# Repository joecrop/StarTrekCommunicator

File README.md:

# StarTrekCommunicator
In the true spirit of Star Trek, this communicator badge is completely autonomous, while fitting in the form factor of an original badge

<a href="https://hackaday.io/project/19700-star-trek-communicator-badge">Hackaday Project</a>

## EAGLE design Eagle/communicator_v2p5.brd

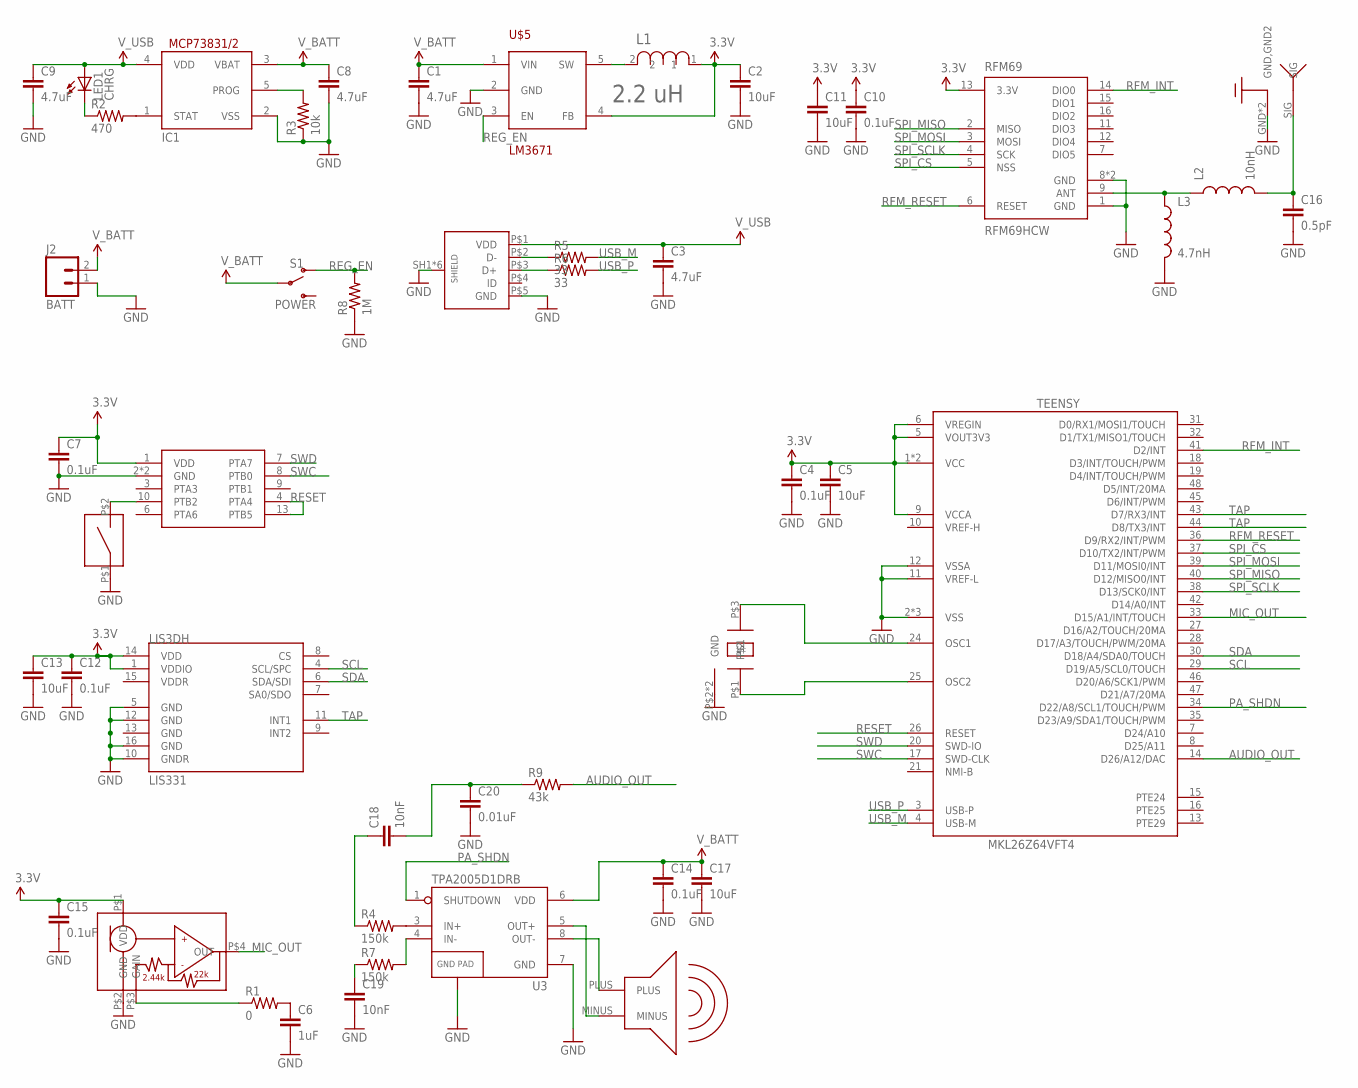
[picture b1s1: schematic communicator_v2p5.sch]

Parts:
3X3MM1: CURRENT_BOOTLOADER3X3MM; QFN50P300X300X100-17N
C1, C3, C8, C9: 4.7uF; 0603-CAP
C2, C5, C11, C13, C17: 10uF; 0603-CAP
C4, C7, C10, C12, C14, C15: 0.1uF; 0603-CAP
C6: 1uF; 0603-CAP
C16: 0.5pF; 0603-CAP
C18, C19: 10nF; 0603-CAP
C20: 0.01uF; 0603-CAP
IC1: MCP73831/OT; SOT23-5L
J2: BATT; 1X02
L1: 2.2 uH; INDC3225X22N
L2: 10nH; 0603
L3: 4.7nH; 0603
LED1: CHRG; CHIPLED_0805
LIS3DH: LIS331; LGA16-3MM
R1: 0; 0603-RES
R2: 470; 0603-RES
R3: 10k; 0603-RES
R4, R7: 150k; 0603-RES
R5, R6: 33; 0603-RES
R8: 1M; 0603-RES
R9: 43k; 0603-RES
RFM69: RFM69HCW; RFM69HCW-XXXS2
S1: POWER; SWITCH_SPST_SMD_A
TEENSY: MKL26Z64VFT4; QFN50P700X700X100-49N
U3: TPA2005D1DRB; QFN-8_PAD
U$1: ANTENNA_915MHZ
U$2: MICROPHONE; SPU0414HR5H-SB
U$3: SPEAKER; PSR1511N08S3K
U$4: KXT131LHS
U$5: LM3671; SOT23-5
U$8: MICRO_USB_B
U$9: TSX-3225

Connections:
3.3V: 3X3MM1.1 (VDD), C2.1, C4.1, C5.1, C7.1, C10.1, C11.1, C12.1, C13.1, C15.1, L1.1, LIS3DH.1 (VDDIO), LIS3DH.14 (VDD), RFM69.13 (3.3V), TEENSY.1 (VCC), TEENSY.5 (VOUT3V3), TEENSY.6 (VREGIN), TEENSY.9 (VCCA), TEENSY.22 (VCC), U$2.P$1 (VDD), U$5.4 (FB)
AUDIO_OUT: R9.2, TEENSY.14 (D26/A12/DAC)
GND: 3X3MM1.2 (GND), 3X3MM1.17 (GND), C1.2, C2.2, C3.2, C4.2, C5.2, C6.2, C7.2, C8.2, C9.2, C10.2, C11.2, C12.2, C13.2, C14.2, C15.2, C16.2, C17.2, C19.2, C20.2, IC1.2 (VSS), J2.1, L3.2, LIS3DH.5 (GND), LIS3DH.10 (GNDR), LIS3DH.12 (GND), LIS3DH.16 (GND), R3.1, R8.1, RFM69.1 (GND), RFM69.8 (GND), RFM69.10 (GND), TEENSY.2 (VSS), TEENSY.11 (VREF-L), TEENSY.12 (VSSA), TEENSY.23 (VSS), TEENSY.49 (VSS), U3.7 (GND), U3.9 (GND), U3.10 (GND), U3.11 (GND), U3.12 (GND), U3.13 (GND), U$1.GND (GND,GND2), U$1.GND2 (GND,GND2), U$2.P$2 (GND), U$4.P$1, U$5.2 (GND), U$8.P$5 (GND), U$8.SH1 (SHIELD), U$8.SH2 (SHIELD), U$8.SH3 (SHIELD), U$8.SH4 (SHIELD), U$8.SH5 (SHIELD), U$8.SH6 (SHIELD), U$9.P$2 (GND), U$9.P$4 (GND)
MIC_OUT: TEENSY.33 (D15/A1/INT/TOUCH), U$2.P$4 (OUT)
unnamed: R1.1, U$2.P$3 (GAIN)
unnamed: IC1.1 (STAT), R2.2
unnamed: C6.1, R1.2
unnamed: C16.1, L2.2, U$1.SIG
unnamed: TEENSY.24 (OSC1), U$9.P$3
unnamed: TEENSY.25 (OSC2), U$9.P$1
unnamed: U3.5 (OUT+), U$3.MINUS
unnamed: L2.1, L3.1, RFM69.9 (ANT)
unnamed: 3X3MM1.10 (PTB2), U$4.P$2
unnamed: U3.8 (OUT-), U$3.PLUS
unnamed: R4.2, U3.3 (IN+)
unnamed: R7.2, U3.4 (IN-)
unnamed: C18.1, R4.1
unnamed: R5.1, U$8.P$2 (D-)
unnamed: R6.1, U$8.P$3 (D+)
unnamed: C19.1, R7.1
unnamed: IC1.5 (PROG), R3.2
unnamed: LED1.C, R2.1
unnamed: L1.2, U$5.5 (SW)
PA_IN: C18.2, C20.1, R9.1
PA_SHDN: TEENSY.34 (D22/A8/SCL1/TOUCH/PWM), U3.1 (SHUTDOWN)
REG_EN: R8.2, S1.1 (O), U$5.3 (EN)
RESET: 3X3MM1.4 (PTA4), 3X3MM1.13 (PTB5), TEENSY.26 (RESET)
RFM_INT: RFM69.14 (DIO0), TEENSY.41 (D2/INT)
RFM_RESET: RFM69.6 (RESET), TEENSY.36 (D9/RX2/INT/PWM)
SCL: LIS3DH.4 (SCL/SPC), TEENSY.29 (D19/A5/SCL0/TOUCH)
SDA: LIS3DH.6 (SDA/SDI), TEENSY.30 (D18/A4/SDA0/TOUCH)
SPI_CS: RFM69.5 (NSS), TEENSY.37 (D10/TX2/INT/PWM)
SPI_MISO: RFM69.2 (MISO), TEENSY.40 (D12/MISO0/INT)
SPI_MOSI: RFM69.3 (MOSI), TEENSY.39 (D11/MOSI0/INT)
SPI_SCLK: RFM69.4 (SCK), TEENSY.38 (D13/SCK0/INT)
SWC: 3X3MM1.8 (PTB0), TEENSY.17 (SWD-CLK)
SWD: 3X3MM1.7 (PTA7), TEENSY.20 (SWD-IO)
TAP: LIS3DH.11 (INT1), TEENSY.43 (D7/RX3/INT), TEENSY.44 (D8/TX3/INT)
USB_M: R5.2, TEENSY.4 (USB-M)
USB_P: R6.2, TEENSY.3 (USB-P)
V_BATT: C1.1, C8.1, C14.1, C17.1, IC1.3 (VBAT), J2.2, S1.2, U3.6 (VDD), U$5.1 (VIN)
V_USB: C3.1, C9.1, IC1.4 (VDD), LED1.A, U$8.P$1 (VDD)

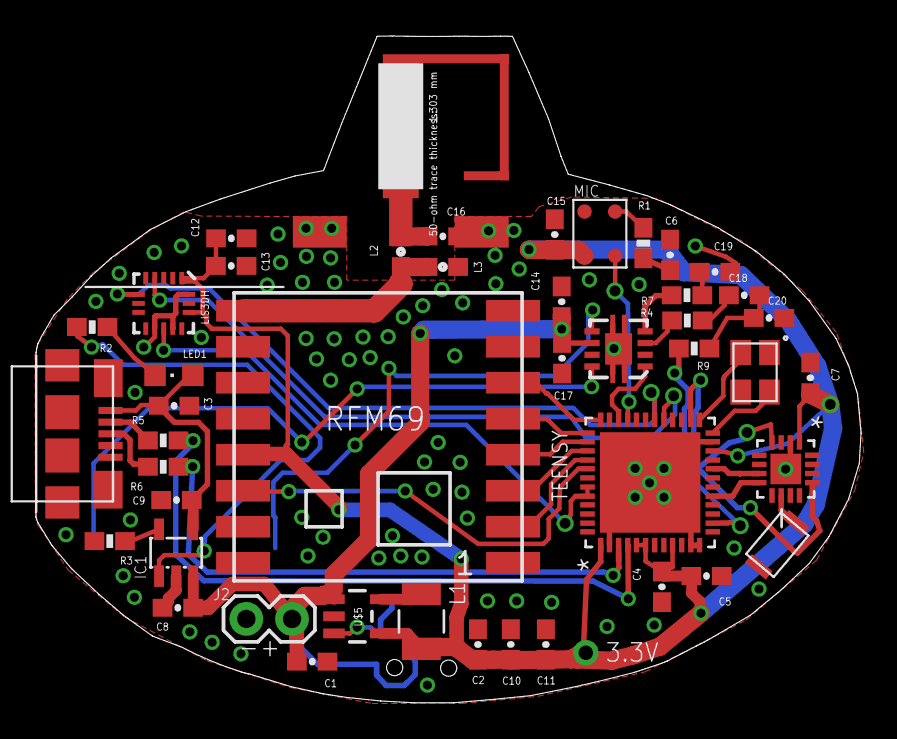
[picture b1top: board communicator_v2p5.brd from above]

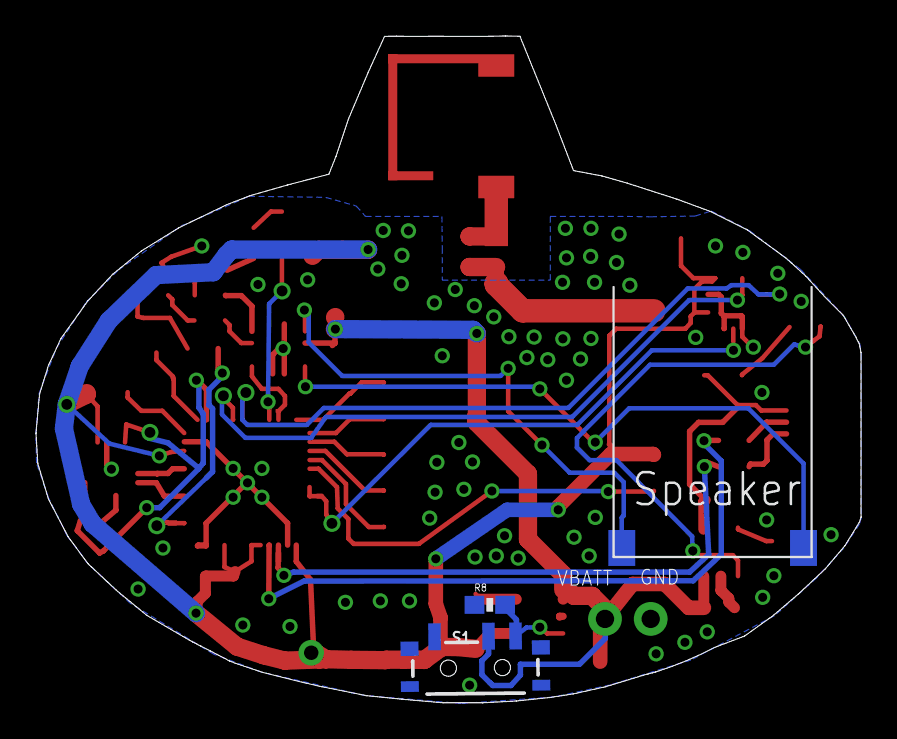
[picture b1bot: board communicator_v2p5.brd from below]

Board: 2 copper layers, 45.8 x 37.0 mm, 48 parts (3 on the bottom side), 42 nets.

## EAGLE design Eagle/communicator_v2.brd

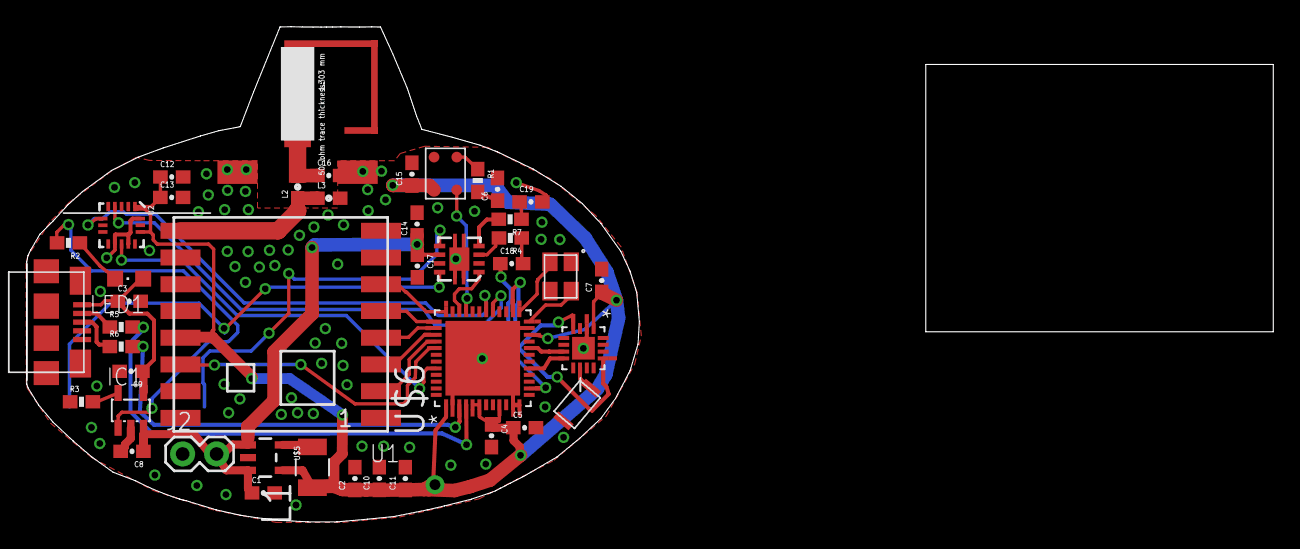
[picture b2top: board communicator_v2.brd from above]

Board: 2 copper layers, 93.3 x 37.0 mm, 45 parts (1 on the bottom side), 40 nets.

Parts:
3X3MM1: CURRENT_BOOTLOADER3X3MM; QFN50P300X300X100-17N
C1, C3, C8, C9: 4.7uF; 0603-CAP
C2, C5, C11, C13, C17: 10uF; 0603-CAP
C4, C7, C10, C12, C14, C15: 0.1uF; 0603-CAP
C6: 1uF; 0603-CAP
C16: 0.5pF; 0603-CAP
C18, C19: 1nF; 0603-CAP
IC1: MCP73831/OT; SOT23-5L
J2: 1X02
L1: 2.2 uH; INDC3225X22N
L2: 10nH; 0603
L3: 4.7nH; 0603
LED1: CHIPLED_0805
R1: 0; 0603-RES
R2: 470; 0603-RES
R3: 2.55k; 0603-RES
R4, R7: 150k; 0603-RES
R5, R6: 33; 0603-RES
U1: RFM69HCW; RFM69HCW-XXXS2
U2: LIS331; LGA16-3MM
U3: TPA2005D1DRB; QFN-8_PAD
U$1: ANTENNA_915MHZ
U$2: MICROPHONE; SPU0414HR5H-SB
U$3: SPEAKER; PSR1511N08S3K
U$4: KXT131LHS
U$5: LM3671; SOT23-5
U$6: MKL26Z64VFT4; QFN50P700X700X100-49N
U$7: LIPO-OUTLINE100; LIPO-100
U$8: MICRO_USB_B
U$9: TSX-3225

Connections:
3.3V: 3X3MM1.1, C2.1, C4.1, C5.1, C7.1, C10.1, C11.1, C12.1, C13.1, C15.1, L1.1, U1.13, U2.1, U2.14, U$2.P$1, U$5.4, U$6.1, U$6.5, U$6.6, U$6.9, U$6.22
AUDIO_OUT: C18.1, U$6.14
GND: 3X3MM1.2, 3X3MM1.17, C1.2, C2.2, C3.2, C4.2, C5.2, C6.2, C7.2, C8.2, C9.2, C10.2, C11.2, C12.2, C13.2, C14.2, C15.2, C16.2, C17.2, C19.2, IC1.2, J2.1, L3.2, R3.1, U1.1, U1.8, U1.10, U2.5, U2.10, U2.12, U2.16, U3.7, U3.9, U3.10, U3.11, U3.12, U3.13, U$1.GND, U$1.GND2, U$2.P$2, U$4.P$1, U$5.2, U$6.2, U$6.11, U$6.12, U$6.23, U$6.49, U$8.P$5, U$8.SH1, U$8.SH2, U$8.SH3, U$8.SH4, U$8.SH5, U$8.SH6, U$9.P$2, U$9.P$4
MIC_OUT: U$2.P$4, U$6.33
unnamed: R1.1, U$2.P$3
unnamed: IC1.1, R2.2
unnamed: C6.1, R1.2
unnamed: C16.1, L2.2, U$1.SIG
unnamed: U$6.24, U$9.P$3
unnamed: U$6.25, U$9.P$1
unnamed: U3.5, U$3.MINUS
unnamed: L2.1, L3.1, U1.9
unnamed: 3X3MM1.10, U$4.P$2
unnamed: U3.8, U$3.PLUS
unnamed: R4.2, U3.3
unnamed: R7.2, U3.4
unnamed: C18.2, R4.1
unnamed: R5.1, U$8.P$2
unnamed: R6.1, U$8.P$3
unnamed: C19.1, R7.1
unnamed: IC1.5, R3.2
unnamed: LED1.C, R2.1
unnamed: L1.2, U$5.5
PA_SHDN: U3.1, U$6.34
RESET: 3X3MM1.4, 3X3MM1.13, U$6.26
RFM_INT: U1.14, U$6.41
RFM_RESET: U1.6, U$6.36
SCL: U2.4, U$6.29
SDA: U2.6, U$6.30
SPI_CS: U1.5, U$6.37
SPI_MISO: U1.2, U$6.40
SPI_MOSI: U1.3, U$6.39
SPI_SCLK: U1.4, U$6.38
SWC: 3X3MM1.8, U$6.17
SWD: 3X3MM1.7, U$6.20
TAP: U2.11, U$6.44
USB_M: R5.2, U$6.4
USB_P: R6.2, U$6.3
V_BATT: C1.1, C8.1, C14.1, C17.1, IC1.3, J2.2, U3.6, U$5.1, U$5.3
V_USB: C3.1, C9.1, IC1.4, LED1.A, U$8.P$1

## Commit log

2017-11-27 arduino/teensy files
2017-11-27 uploading 3d models, arduino code and pub files
2018-01-15 corrected library versions
    RFM69 library versions (especially RFM69_stream) were wrong. They are
    not the most up to date thanks to backups. Communicator code is also
    updated to version BETA2
2018-01-15 added new methods to library
2018-01-17 added arduino new libraries
    added new libraries

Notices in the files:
parts and their libraries:
SparkFun-Capacitors: Licensing: Creative Commons ShareAlike 4.0 International - https://creativecommons.org/licenses/by-sa/4.0
